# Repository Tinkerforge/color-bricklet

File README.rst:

Color Bricklet
==============

This repository contains the firmware source code and the hardware design
files. The documentation generator configs can be found at
https://github.com/Tinkerforge/generators

Repository Content
------------------

software/:
 * examples/: Examples for all supported languages
 * build/: Compiled files
 * src/: Source code of firmware
 * Makefile: Makefile to build project

hardware/:
 * Contains KiCad project files and additionally schematics as PDF

datasheets/:
 * Contains datasheets for sensors and complex ICs that are used

Hardware
--------

The hardware is designed with the open source EDA Suite KiCad
(http://www.kicad.org). Before you are able to open the files,
you have to install the Tinkerforge kicad-libraries
(https://github.com/Tinkerforge/kicad-libraries). You can either clone
them directly in hardware/ or clone them in a separate folder and
symlink them into hardware/
(ln -s kicad_path/kicad-libraries project_path/hardware). After that you
can open the .pro file in hardware/ with KiCad and from there view and
modify the schematics and the PCB layout.

Software
--------

If you want to do your own Brick/Bricklet firmware development we highly
recommend that you use our build environment setup script and read the
tutorial (https://www.tinkerforge.com/en/doc/Tutorials/Tutorial_Build_Environment/Tutorial.html).

To compile the C code we recommend you to install the newest GNU Arm Embedded
Toolchain (https://launchpad.net/gcc-arm-embedded/+download).
You also need to install bricklib (https://github.com/Tinkerforge/bricklib)
and brickletlib (https://github.com/Tinkerforge/brickletlib).

You can either clone it directly in software/src/ or clone it in a
separate folder and symlink it into software/src/
(ln -s bricklib_path/bricklib project_path/software/src/ and
ln -s brickletlib_path/brickletlib project_path/software/src/).
Finally make sure to have CMake installed
(http://www.cmake.org/cmake/resources/software.html).

After that you can build the firmware by invoking make in software/.
The firmware (.bin) can then be found in software/build/ and uploaded
with brickv (click button "Flashing" on start screen).

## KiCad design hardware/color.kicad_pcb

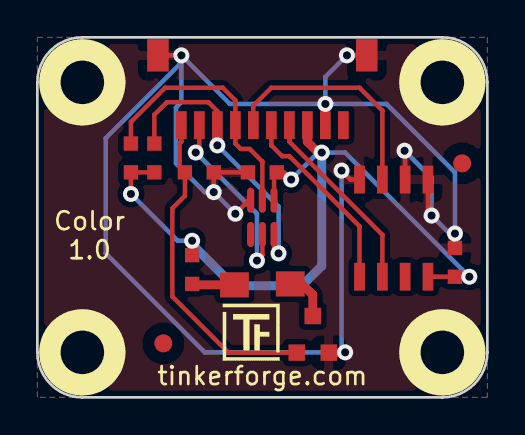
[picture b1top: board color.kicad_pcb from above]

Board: 2 copper layers, 25.0 x 20.0 mm, 19 parts (2 on the bottom side), 11 nets.

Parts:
C1, C2: 100nF; C0603
D1: LED; LED-3x2
Fiducial_Mark: VAL**; Fiducial_Mark
Fiducial_Mark#2: VAL**; Fiducial_Mark
P1: CON-SENSOR
Q1: 2N7002P; SOT23GDS
R1: 10k; R0603
R2: 180; R0603
R3, R4: 2k2; R0603
U1: TCS3472; FN-TCS3472
U2: M24C64; SOIC8
U3, U4, U5, U6: DRILL; DRILL_NP
VAL: WEEE_7mm
VAL#2: CE_5mm

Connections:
GND: C1.2, C2.2, P1.2, P1.EP, Q1.S, R1.2, U1.3, U2.1, U2.2, U2.4
unnamed: D1.1, R2.2
unnamed: D1.2, Q1.D
unnamed: P1.6, U2.3
unnamed: P1.7, R3.2, U1.2
unnamed: P1.8, R4.2, U1.6
unnamed: P1.9, U1.5
unnamed: P1.10, Q1.G, R1.1
SCL: P1.4, U2.6
SDA: P1.5, U2.5
VCC: C1.1, C2.1, P1.3, R2.1, R3.1, R4.1, U1.1, U2.8

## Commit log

2014-02-25 Add TCS34725 datasheet
2014-03-06 color-bricklet: commit initial source code and python examples
2014-03-06 color-bricklet: adding cmake file for build
2014-03-06 python: adding color-bricklet examples
2014-03-06 color-bricklet: adding C examples
2014-03-06 python: fixed color-bricklet example comments
2014-03-06 c: fixed example comment
2014-03-06 Add getter for color temperature and illuminance
2014-03-07 Use BC_local to save some flash
2014-03-07 Remove destructor
2014-03-07 Add Callbacks for Illuminance and ColorTemperature
2014-03-10 c: modified threshold example
2014-03-10 python: modifying threshold example
2014-03-10 c: fixed threshold example comment
2014-03-10 python: fixed threshold example comment
2014-03-10 perl: adding examples for color bricklet
2014-03-10 javascript: adding color bricklet examples
2014-03-10 c: fixed comment
2014-03-10 java: adding color bricklet examples
2014-03-10 javascript: edit comments in examples
2014-03-10 python: edit example
2014-03-10 csharp: adding color bricklet examples
2014-03-10 php: adding color bricklet examples
2014-03-10 ruby: adding color bricklet examples
2014-03-10 delphi: adding color bricklet examples
2014-03-10 shell: adding color bricklet examples
2014-03-10 vbnet: adding colot bricklet examples
2014-03-11 hardware files for color sensor bricklet
2014-03-12 add missing logo
2014-04-02 java: Unify constants style
2014-04-02 perl: Unify print style
2014-04-03 Some whitespace cleanup
2014-04-11 change pinout according to new prototype
2014-04-11 add pull up resistors
2014-05-23 change default to 60x gain
2014-05-27 add missing fiducials
2014-07-08 fix component value and reference position
2014-07-15 java: Replace System.console() usage with an Eclipse compatible pattern
2014-08-01 Use version 2.0.0 as initial version (it uses protocol 2.0)
2014-08-04 Make sure illuminance can't be negative
2014-08-05 Add missing example, unify existong examples and fix threshold value order
2014-08-05 javascript: Break long lines in HTML examples
2014-08-05 vbnet: Fix wrong variable type in example
2014-08-05 perl: Fix typo
2014-08-05 labview: Fix image file names
2014-08-06 Some whitespace cleanup in examples
2014-10-27 Use constants for the is_light_on return value
    The return value is not bool (it could have been), but an uint8 with
    constants.
2014-11-13 Use up-to-date RGB values in color temperature and illuminance calculation
    Before the last values were used which are only updated if the color
    collback is enabled.
2014-12-02 Use ReadLine instead of ReadKey for C# example
2015-02-13 vbnet: Use ReadLine instead of ReadKey
    Because ReadKey doesn't work with a pipe as stdin on the RED Brick.
2015-03-02 windows: Stop cmake from searching for mingw32-make.exe
    Using MinGW Makefiles as generator makes cmake search for mingw32-make.exe
    which might not be installed because GnuWin32's make.exe is used instead.
2015-05-04 Fix typos
2015-06-18 Whitespace cleanup in examples
2015-07-23 Make JavaScript browser example textarea readonly
2015-07-27 Cleanup C/C++, C#, Java, Python and Ruby examples
2015-07-29 Reformat changelog
2015-08-07 Use full device class name in Python examples
2015-08-12 Fix minor warnings in C/C++ examples
2015-08-14 Cleanup Delphi examples
2015-08-18 Cleanup VB.NET examples
2015-08-19 Cleanup Perl examples
2015-09-09 Duplicate cmake call to fix bug during cmake creation
2015-09-25 run drc
2015-09-30 Generator based example cleanup
2015-11-12 matlab: Fix callback handling for R2014a
    http://undocumentedmatlab.com/blog/matlab-callbacks-for-java-events-in-r2014a
2015-11-25 Include date and commit into changelog
2015-11-30 vbnet: Break long line
2016-05-18 c: Add missing device destroy call
2016-06-29 Whitespace
2016-07-01 Make the change UID comment more explicit
2017-04-13 csharp: Adapt example
2017-04-21 shell: Adapt example
2017-06-02 octave: Use javaObject instead of deprecated java_new
2017-08-01 Add 3d information (final)
2017-08-01 Add 3d model (*.step & *.FCStd)
2017-11-30 Update examples from generator
2017-12-07 mathematica: Also generate .nb files
2018-02-02 Update examples
2018-02-19 javascript: Close div tag correctly
2018-02-20 Cleanup KiCad libraries config
    Ensure LibDir=kicad-libraries and LibName1=tinkerforge.
    Remove special library.
2018-05-24 perl: Use strict in examples
2018-05-28 mathematica: Reorder some lines for clearity
2018-06-27 Remove "in development" tag
2018-07-11 Add Makefile with docker support
2018-07-11 Remove obsolete generate_makefile scripts
2018-07-11 Update directory structure and build instructions
2018-11-06 Add rust examples
2018-11-07 rust: Accept host names for ip connection, fix naming inconsistencies
2018-11-07 rust: Rename callback receivers.
2018-12-14 Add go examples.
2018-12-18 go: Change import path.
2018-12-18 go: Change import path again.
2018-12-20 rust: Fix result variable names in examples.
2019-01-24 mqtt: Add examples.
2019-01-24 mqtt: Fix example header.
2019-01-24 mqtt: Remove executable bit in example permissions.
2019-01-24 go: Minor example fixes.
2019-01-24 mqtt: Minor example fixes.
2019-02-21 fixed library, added sym lib table
2019-03-28 mqtt: Fix whitespace.
2019-08-22 c: Adapt to bindings changes
2020-01-13 examples: Use python3 input instead of python2 raw_input.
2020-01-13 examples: mqtt: Remove trailing whitespace.
2021-10-25 Update KiCad link
    https://www.kicad.org/blog/2021/10/Avoid-links-to-former-kicad-domain/
2022-05-10 go: Fix format string
2022-07-06 Add license files.

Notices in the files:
hardware/color.kicad_pcb:
Licensed under CERN OHL v.1.1
Copyright (©) 2014, B.Nordmeyer
Copyright Tinkerforge GmbH 2014.
This documentation describes Open Hardware and is licensed under the
CERN OHL v. 1.1.
